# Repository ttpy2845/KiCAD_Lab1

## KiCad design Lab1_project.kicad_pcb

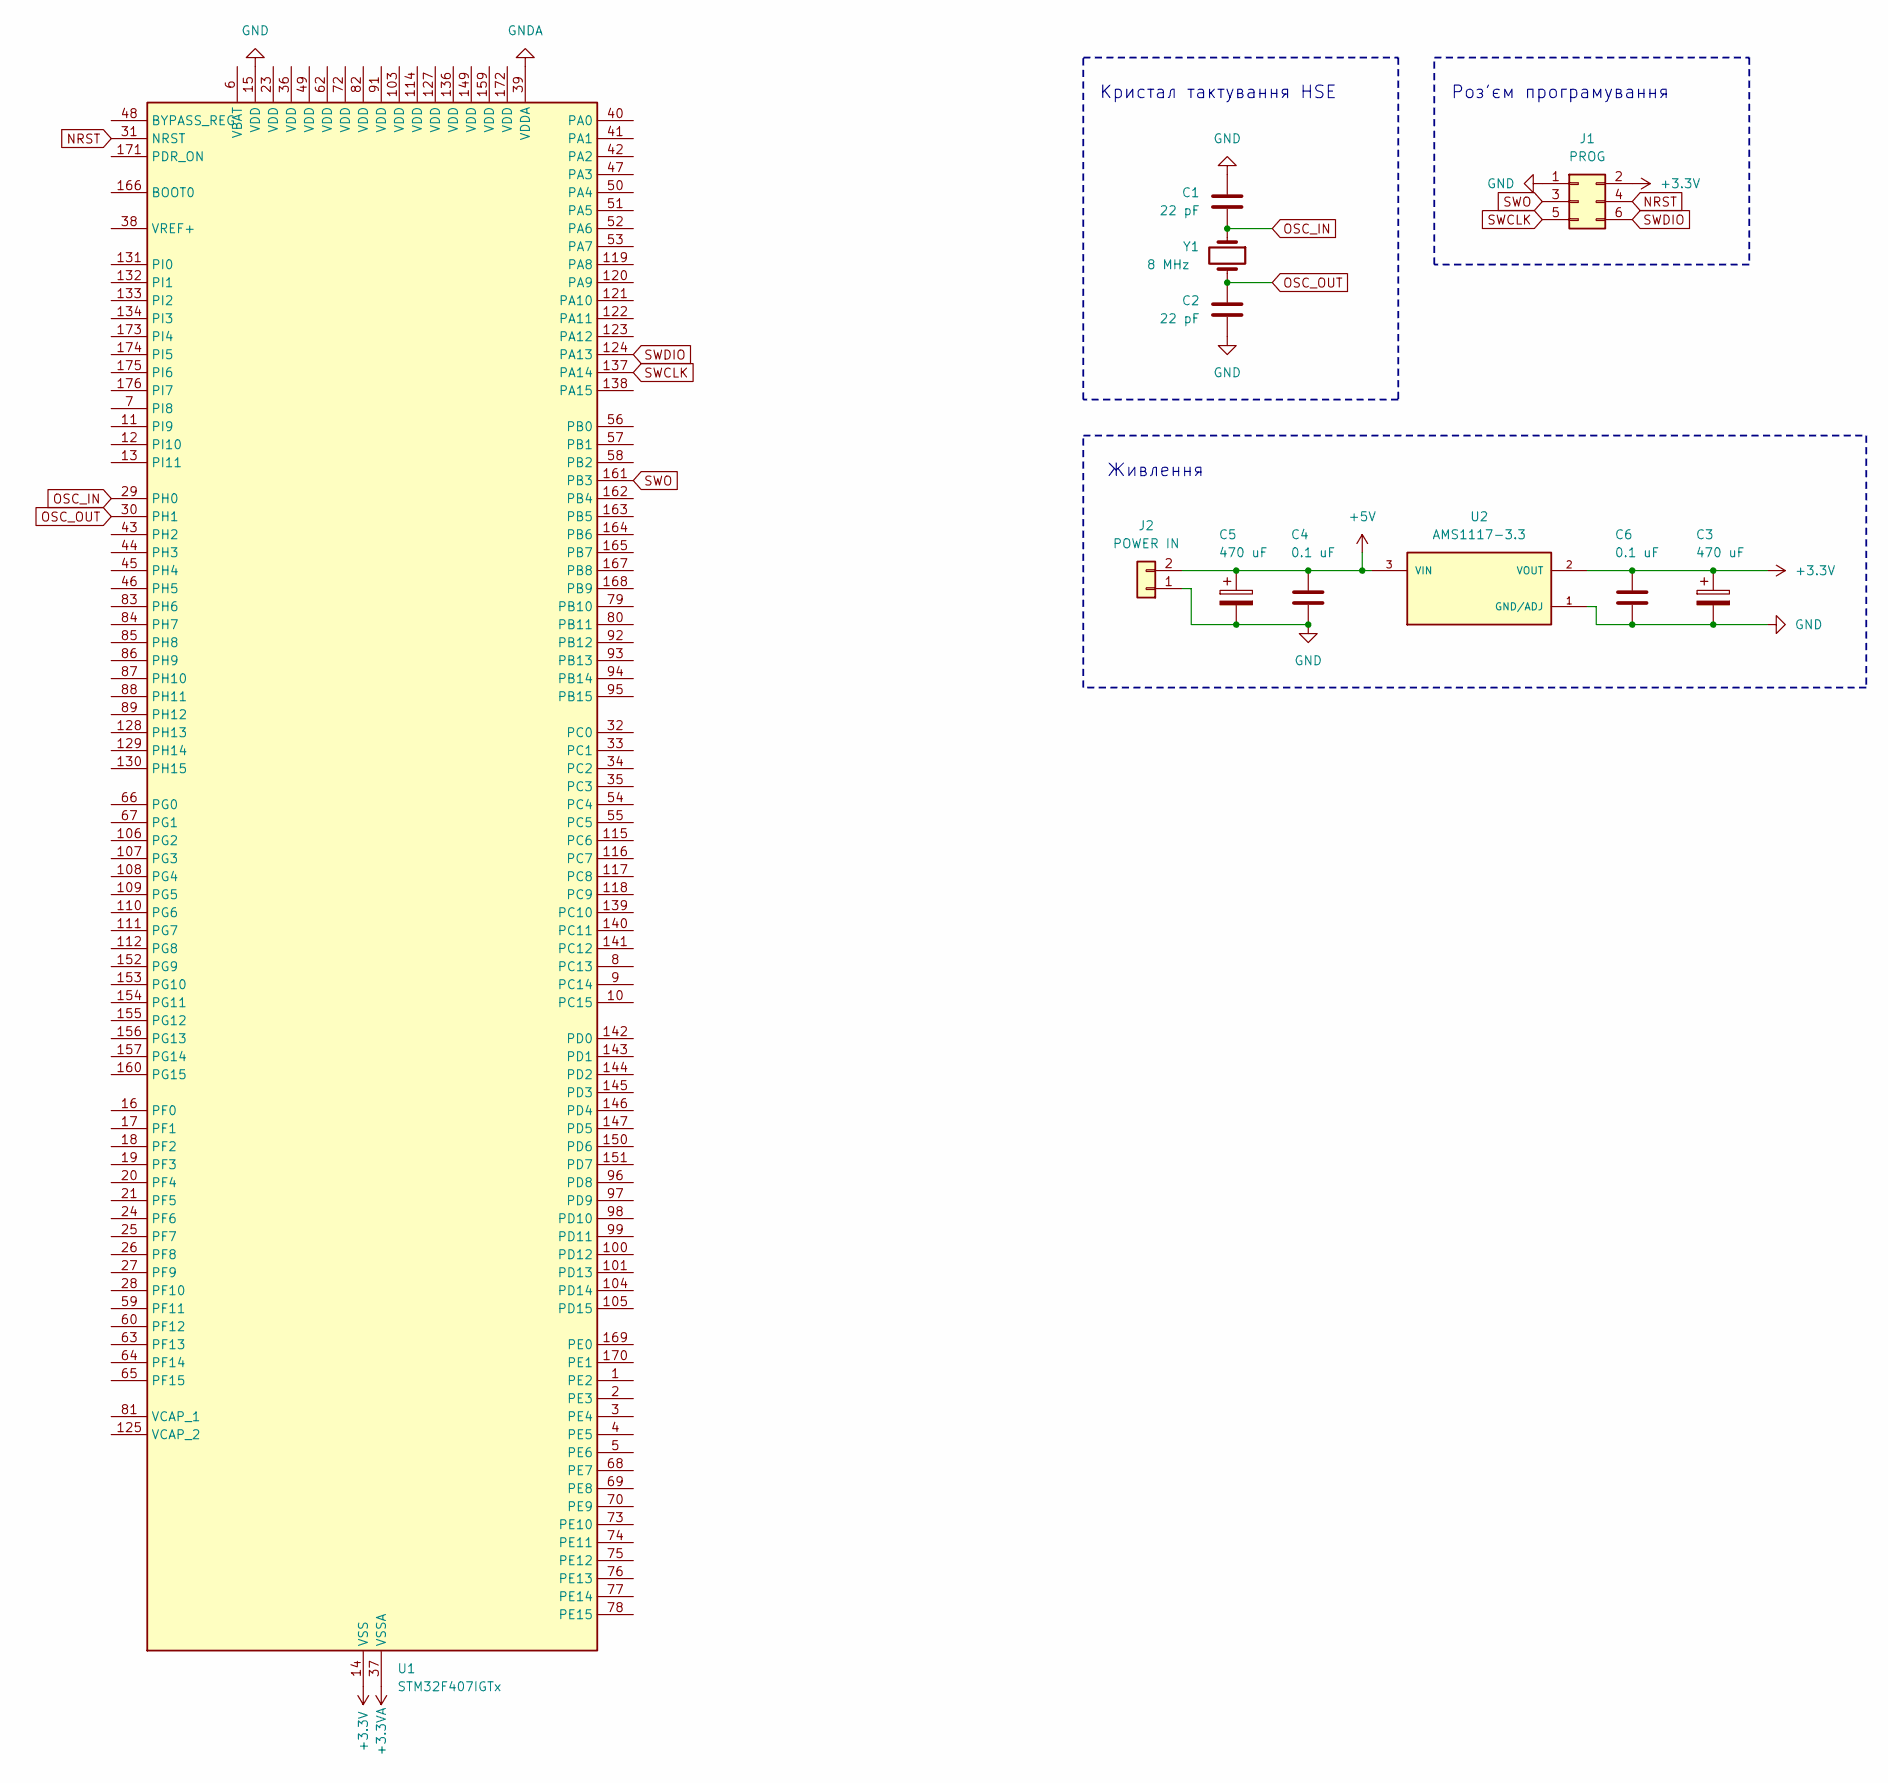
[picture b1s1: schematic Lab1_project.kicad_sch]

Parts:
C1, C2: 22 pF; C_1206_3216Metric_Pad1.33x1.80mm_HandSolder
C3, C5: 470 uF; CP_Radial_D8.0mm_P3.80mm
C4, C6: 0.1 uF; C_1206_3216Metric_Pad1.33x1.80mm_HandSolder
J1: PROG; PinHeader_2x03_P2.54mm_Vertical
J2: POWER IN; JST_XH_B2B-XH-A_1x02_P2.50mm_Vertical
U1: STM32F407IGTx; LQFP-176_24x24mm_P0.5mm
U2: AMS1117-3.3; SOT-223-3_TabPin2; PARTREV N/A
Y1: 8 MHz; Crystal_HC18-U_Vertical

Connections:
+3.3V: C3.1, C6.1, J1.2, U1.14 (VSS), U1.22 (VSS), U1.61 (VSS), U1.71 (VSS), U1.90 (VSS), U1.102 (VSS), U1.113 (VSS), U1.126 (VSS), U1.135 (VSS), U1.148 (VSS), U1.158 (VSS), U2.2 (VOUT)
+3.3VA: U1.37 (VSSA)
+5V: C4.1, C5.1, J2.2, U2.3 (VIN)
GND: C1.1, C2.2, C3.2, C4.2, C5.2, C6.2, J1.1, J2.1, U1.15 (VDD), U2.1 (GND/ADJ)
GNDA: U1.39 (VDDA)
NRST: J1.4, U1.31 (NRST)
OSC_IN: C1.2, U1.29 (PH0), Y1.1
OSC_OUT: C2.1, U1.30 (PH1), Y1.2
SWCLK: J1.5, U1.137 (PA14)
SWDIO: J1.6, U1.124 (PA13)
SWO: J1.3, U1.161 (PB3)

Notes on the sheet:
Живлення
Роз'єм програмування
Кристал тактування HSE

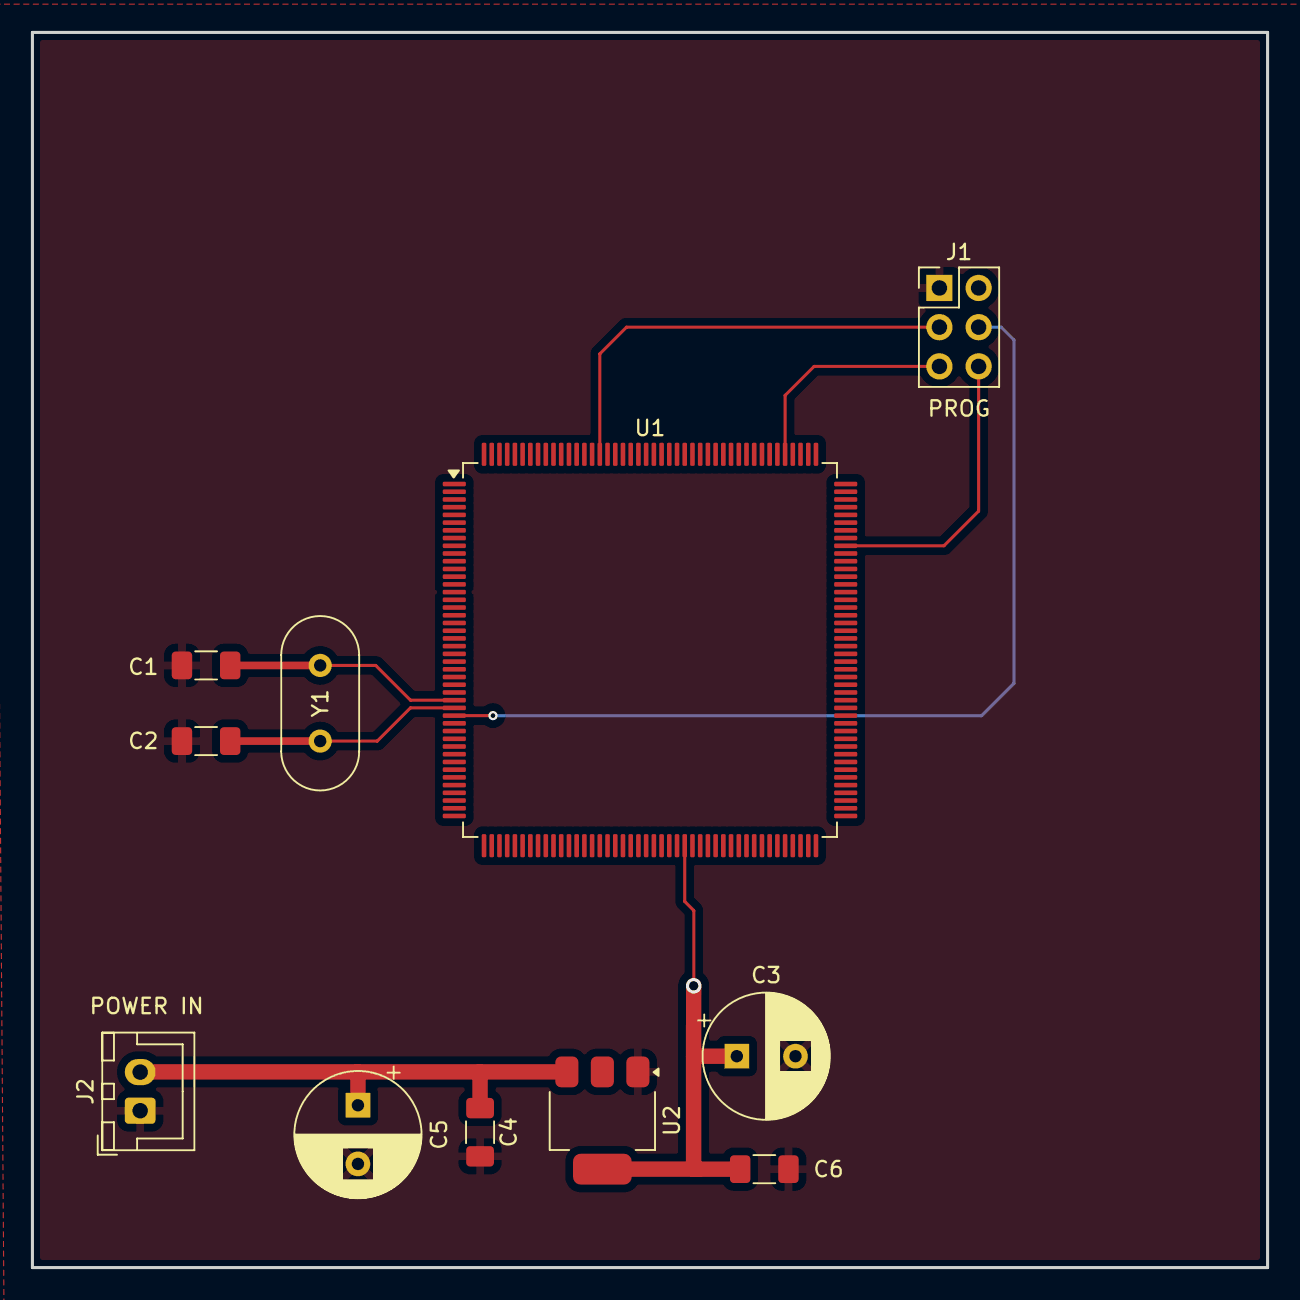
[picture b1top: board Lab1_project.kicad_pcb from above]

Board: 2 copper layers, 80.0 x 80.0 mm, 11 parts (0 on the bottom side), 9 nets.

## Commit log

2026-03-04 Init commit
2026-03-15 fix: GND area, silkscreen
